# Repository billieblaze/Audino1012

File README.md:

Audino1012
==========

Arduino Audio / CV with 10bit ADC and 12bit DAC 

uses 24lc256 RAM and max5250 DAC

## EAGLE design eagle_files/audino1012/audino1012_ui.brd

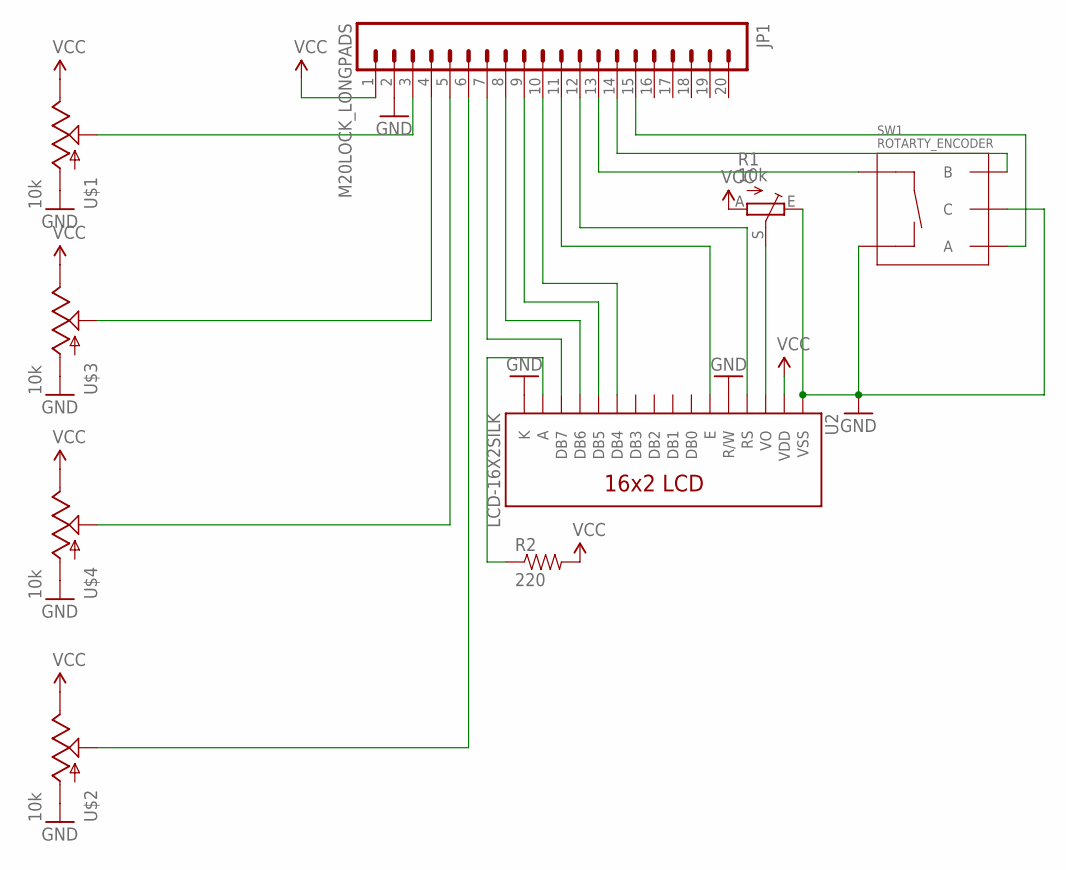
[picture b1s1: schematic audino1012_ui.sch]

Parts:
JP1: M20LOCK_LONGPADS; 1X20_LOCK_LONGPADS
R1: 10k; RJ9W
R2: 220; AXIAL-0.3-KIT
SW1: ROTARTY_ENCODER; ROTARY_ENC_PLAIN
U2: LCD-16X2SILK; LCD-16X2
U$1, U$2, U$3, U$4: 10k; ALPS_POT

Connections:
GND: JP1.2, R1.E, SW1.C, SW1.SW-, U2.1 (VSS), U2.5 (R/W), U2.16 (K), U$1.P$3 (A), U$2.P$3 (A), U$3.P$3 (A), U$4.P$3 (A)
unnamed: JP1.3, U$1.P$2 (S)
unnamed: JP1.4, U$3.P$2 (S)
unnamed: JP1.5, U$4.P$2 (S)
unnamed: JP1.6, U$2.P$2 (S)
unnamed: JP1.7, U2.14 (DB7)
unnamed: JP1.8, U2.13 (DB6)
unnamed: JP1.9, U2.12 (DB5)
unnamed: JP1.10, U2.11 (DB4)
unnamed: JP1.11, U2.6 (E)
unnamed: JP1.12, U2.4 (RS)
unnamed: R1.S, U2.3 (VO)
unnamed: JP1.13, SW1.SW+
unnamed: JP1.14, SW1.B
unnamed: JP1.15, SW1.A
unnamed: R2.P$1 (1), U2.15 (A)
VCC: JP1.1, R1.A, R2.P$2 (2), U2.2 (VDD), U$1.P$1 (E), U$2.P$1 (E), U$3.P$1 (E), U$4.P$1 (E)

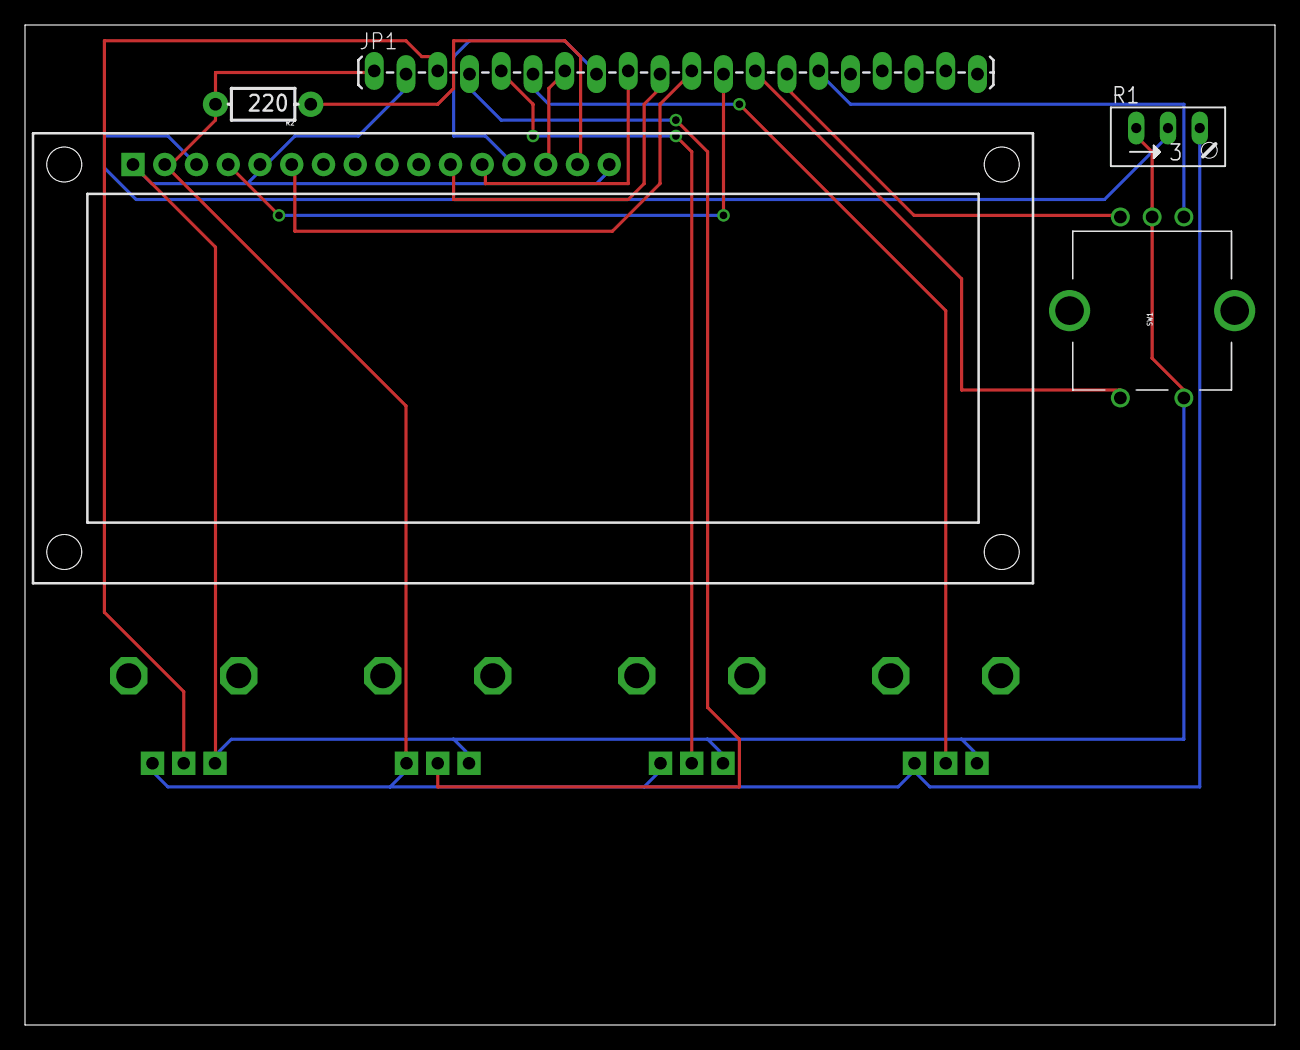
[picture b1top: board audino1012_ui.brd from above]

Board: 2 copper layers, 100.0 x 80.0 mm, 9 parts (0 on the bottom side), 17 nets.

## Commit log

2012-12-12 initial commit - waveforms, eeprom, lcd, menu, adc, dac all in place
2012-12-15 added phi_prompt menu system, envelope, tweaked interrupt
2012-12-15 tweaked playback routines / envelopes.. added many wavetable parameters
2012-12-17 implemented basic midi functionality and worked on menu layout
2012-12-20 added potentiometers and updated service loop a bit - samples now render straight from eeprom
2012-12-22 changed menu, ram optimization,
2012-12-22 menu stuff
2012-12-22 fixed menu bugs! reorg'd variable declarations
2012-12-23 moved wavetable to local eeprom - will use external for saving patches, but playback is faster and playback tempspace can go away!
2013-01-03 misc
2013-01-03 started schematics

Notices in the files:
parts and their libraries:
SparkFun-Displays: Licensing: CC v3.0 Share-Alike You are welcome to use this library for commercial purposes.
